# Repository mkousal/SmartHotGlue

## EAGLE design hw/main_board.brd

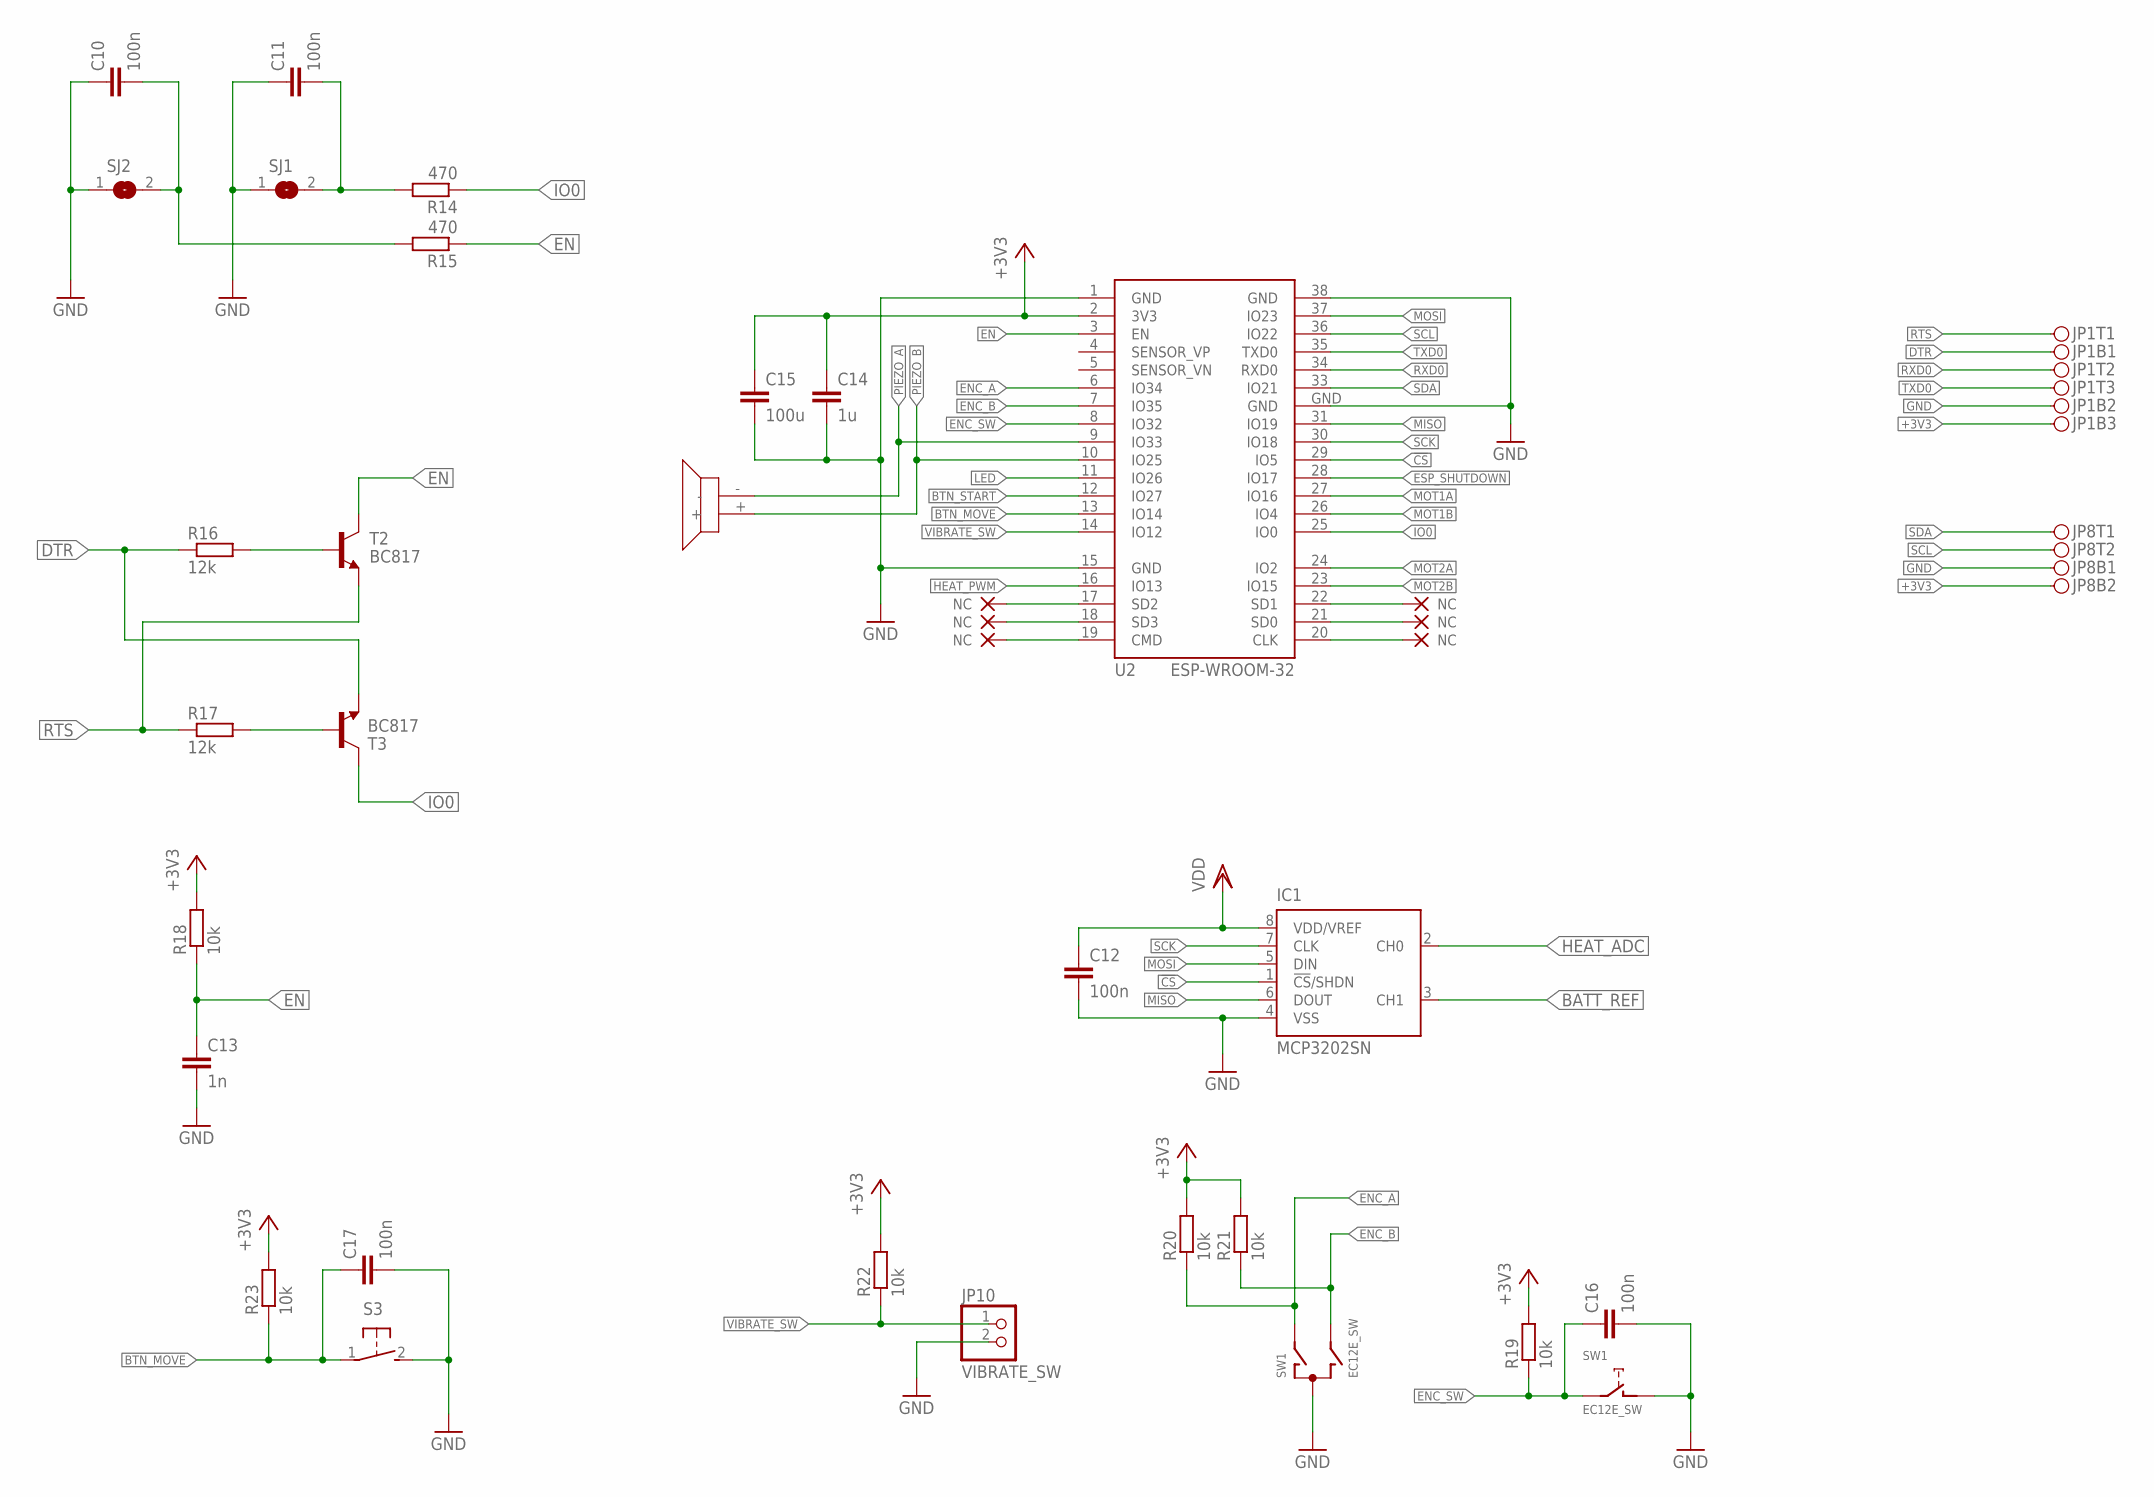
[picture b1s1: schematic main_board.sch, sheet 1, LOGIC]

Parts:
C10, C11, C12, C16, C17: 100n; C0603
C13: 1n; C0603
C14: 1u; C0603
C15: 100u; C0603
IC1: MCP3202SN; SO-08
JP1: PINH2X03; PINH2X03SMD
JP8: PINH2X02; PINH2X02SMD
JP10: VIBRATE_SW; 1X02
R14, R15: 470; R0603
R16, R17: 12k; R0603
R18, R19, R20, R21, R22, R23: 10k; R0603
S3: 31-XX; B3F-31XX
SJ1, SJ2: SJ
SW1: EC12E_SW; ALPS_EC12E_SW
T2, T3: BC817; SOT23-BEC
U2: ESP-WROOM-32
U$1: PIEZO

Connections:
!CS: IC1.1 (!CS!/SHDN), U2.29 (IO5)
+3V3: C14.1, C15.1, JP1.B3, JP8.B2, R18.2, R19.2, R20.2, R21.2, R22.2, R23.2, U2.2 (3V3); also elsewhere on the board
BATT_REF: IC1.3 (CH1); also elsewhere on the board
BTN_MOVE: C17.1, R23.1, S3.1, U2.13 (IO14)
BTN_START: U2.12 (IO27)
DTR: JP1.B1, R16.1, T3.E
EN: C13.1, R15.1, R18.1, T2.C, U2.3 (EN); also elsewhere on the board
ENC_A: R20.1, SW1.A, U2.6 (IO34)
ENC_B: R21.1, SW1.B, U2.7 (IO35)
ENC_SW: C16.1, R19.1, SW1.E (2), U2.8 (IO32)
ESP_SHUTDOWN: U2.28 (IO17); also elsewhere on the board
GND: C10.1, C11.1, C12.2, C13.2, C14.2, C15.2, C16.2, C17.2, IC1.4 (VSS), JP1.B2, JP8.B1, JP10.2, S3.2 (S), SJ1.1, SJ2.1, SW1.C, SW1.D (1), U2.1 (GND), U2.15 (GND), U2.38 (GND), U2.GND; also elsewhere on the board
HEAT_ADC: IC1.2 (CH0); also elsewhere on the board
HEAT_PWM: U2.16 (IO13); also elsewhere on the board
IO0: R14.1, T3.C, U2.25 (IO0)
LED: U2.11 (IO26)
MISO: IC1.6 (DOUT), U2.31 (IO19)
MOSI: IC1.5 (DIN), U2.37 (IO23)
MOT1A: U2.27 (IO16); also elsewhere on the board
MOT1B: U2.26 (IO4); also elsewhere on the board
MOT2A: U2.24 (IO2); also elsewhere on the board
MOT2B: U2.23 (IO15); also elsewhere on the board
unnamed: R16.2, T2.B
unnamed: C10.2, R15.2, SJ2.2
unnamed: R17.2, T3.B
unnamed: C11.2, R14.2, SJ1.2
PIEZO_A: U2.9 (IO33), U$1.-
PIEZO_B: U2.10 (IO25), U$1.+
RTS: JP1.T1, R17.1, T2.E
RXD0: JP1.T2, U2.34 (RXD0)
SCK: IC1.7 (CLK), U2.30 (IO18)
SCL: JP8.T2, U2.36 (IO22)
SDA: JP8.T1, U2.33 (IO21)
TXD0: JP1.T3, U2.35 (TXD0)
VDD: C12.1, IC1.8 (VDD/VREF); also elsewhere on the board
VIBRATE_SW: JP10.1, R22.1, U2.14 (IO12)

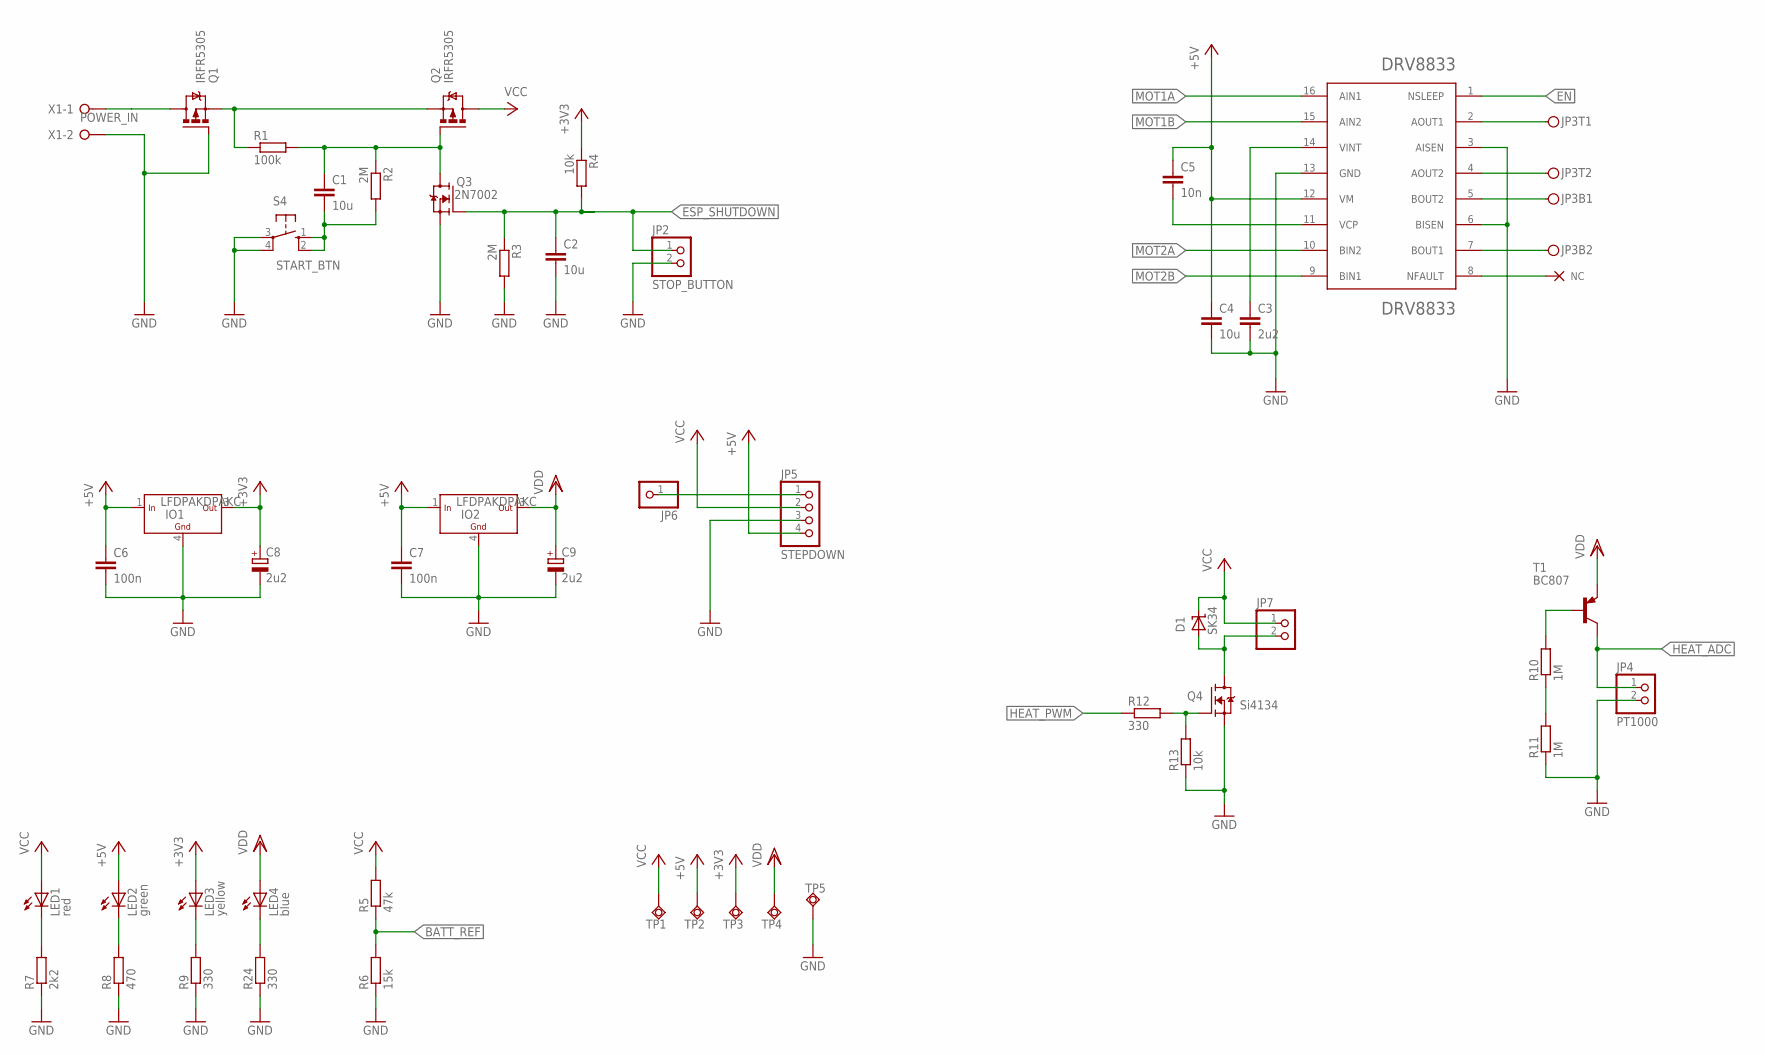
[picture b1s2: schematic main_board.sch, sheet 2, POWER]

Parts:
C1, C2: 10u; C0805
C3: 2u2; C0603
C4: 10u; C1206
C5: 10n; C0603
C6, C7: 100n; C0603
C8, C9: 2u2; UD-4X5,8_NICHICON
D1: SK34; SMB
DRV8833PWP1: DRV8833; SOP65P640X120-17N
IO1, IO2: LFDPAKDPAKC; DPAK
JP2: STOP_BUTTON; 1X02
JP3: PINH2X02; PINH2X02SMD
JP4: PT1000; 1X02
JP5: STEPDOWN; 1X04
JP6: PINHD-1X1; 1X01
JP7: PINHD-1X2; 1X02
LED1: red; CHIP-LED0603
LED2: green; CHIP-LED0603
LED3: yellow; CHIP-LED0603
LED4: blue; CHIP-LED0603
Q1, Q2: IRFR5305; D-PAK_TO252AA
Q3: 2N7002; SOT23
Q4: Si4134; SO-8
R1: 100k; R0603
R2, R3: 2M; R0603
R4, R13: 10k; R0603
R5: 47k; R0603
R6: 15k; R0603
R7: 2k2; R0603
R8: 470; R0603
R9, R12, R24: 330; R0603
R10, R11: 1M; R0603
S4: START_BTN; B3F-10XX
T1: BC807; SOT23-BEC
TP1, TP2, TP3, TP4, TP5: TPSQTP20SQ; TP20SQ
X1: POWER_IN; W237-132

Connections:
+3V3: C8.+, IO1.3 (OUT), LED3.A, R4.1, TP3.TP; also elsewhere on the board
+5V: C4.1, C5.1, C6.1, C7.1, DRV8833PWP1.12 (VM), IO1.1 (IN), IO2.1 (IN), JP5.4, LED2.A, TP2.TP
BATT_REF: R5.1, R6.2; also elsewhere on the board
EN: DRV8833PWP1.1 (NSLEEP); also elsewhere on the board
ESP_SHUTDOWN: C2.1, JP2.1, Q3.1 (G), R3.1, R4.2; also elsewhere on the board
GND: C2.2, C3.2, C4.2, C6.2, C7.2, C8.-, C9.-, DRV8833PWP1.3 (AISEN), DRV8833PWP1.6 (BISEN), DRV8833PWP1.13 (GND), IO1.4 (GND), IO2.4 (GND), JP2.2, JP4.2, JP5.3, Q1.1 (G), Q3.2 (S), Q4.1 (S), Q4.2 (S), Q4.3 (S), R3.2, R6.1, R7.1, R8.1, R9.1, R11.1, R13.1, R24.1, S4.3, S4.4 (P1), TP5.TP, X1.2; also elsewhere on the board
HEAT_ADC: JP4.1, T1.C; also elsewhere on the board
HEAT_PWM: R12.1; also elsewhere on the board
MOT1A: DRV8833PWP1.16 (AIN1); also elsewhere on the board
MOT1B: DRV8833PWP1.15 (AIN2); also elsewhere on the board
MOT2A: DRV8833PWP1.10 (BIN2); also elsewhere on the board
MOT2B: DRV8833PWP1.9 (BIN1); also elsewhere on the board
unnamed: Q1.3 (S), Q2.3 (S), R1.1
unnamed: C1.1, Q2.1 (G), Q3.3 (D), R1.2, R2.1
unnamed: LED4.C, R24.2
unnamed: Q1.4 (D), X1.1
unnamed: LED3.C, R9.2
unnamed: LED2.C, R8.2
unnamed: LED1.C, R7.2
unnamed: DRV8833PWP1.2 (AOUT1), JP3.T1
unnamed: DRV8833PWP1.4 (AOUT2), JP3.T2
unnamed: DRV8833PWP1.5 (BOUT2), JP3.B1
unnamed: DRV8833PWP1.7 (BOUT1), JP3.B2
unnamed: C3.1, DRV8833PWP1.14 (VINT)
unnamed: JP5.1, JP6.1
unnamed: C5.2, DRV8833PWP1.11 (VCP)
unnamed: D1.A, JP7.2, Q4.5 (D), Q4.6 (D), Q4.7 (D), Q4.8 (D)
unnamed: R10.1, R11.2
unnamed: R10.2, T1.B
unnamed: Q4.4 (G), R12.2, R13.2
unnamed: C1.2, R2.2, S4.1 (S), S4.2 (S1)
VCC: D1.C, JP5.2, JP7.1, LED1.A, Q2.4 (D), R5.2, TP1.TP
VDD: C9.+, IO2.3 (OUT), LED4.A, T1.E, TP4.TP; also elsewhere on the board

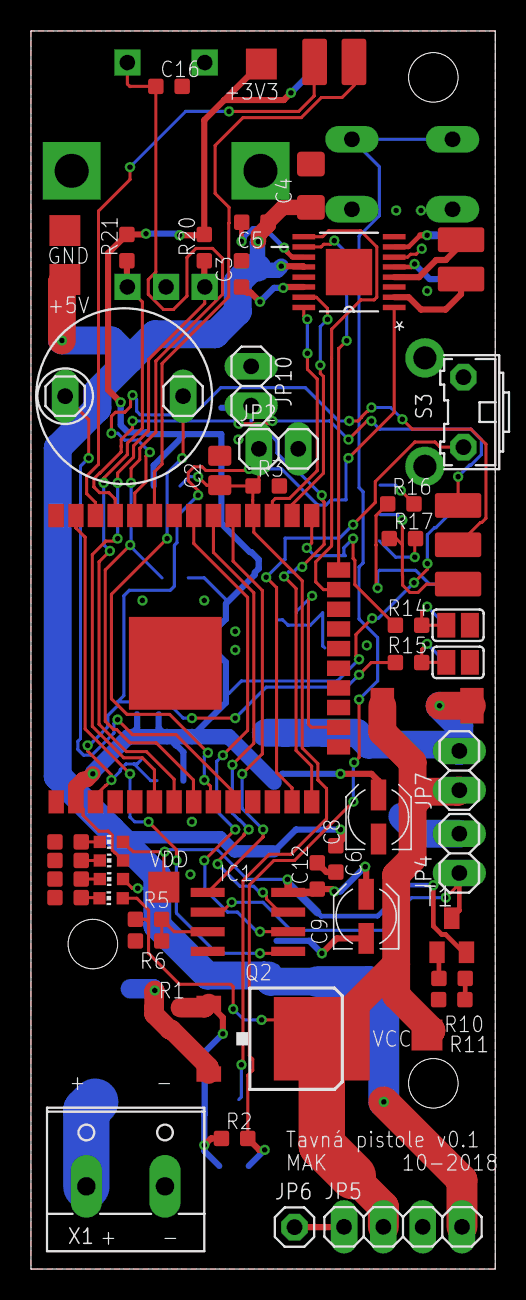
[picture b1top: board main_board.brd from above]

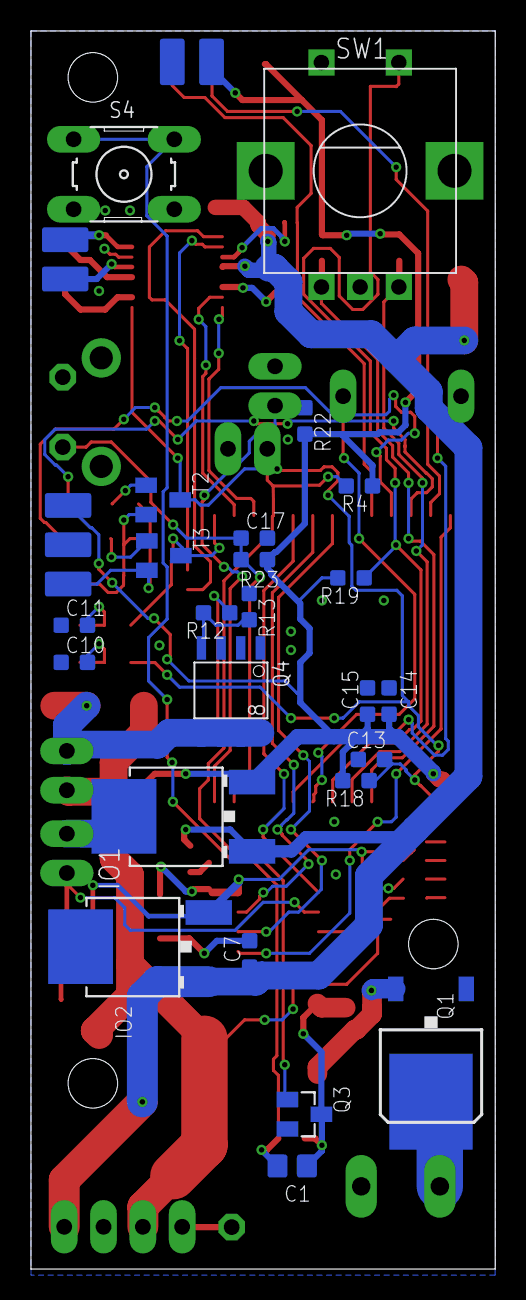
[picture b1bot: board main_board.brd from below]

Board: 2 copper layers, 30.0 x 80.0 mm, 79 parts (24 on the bottom side), 55 nets.

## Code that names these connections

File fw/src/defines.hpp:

#define CS_MCP3202 5
#define PIN_SDA 21
#define PIN_SCL 22
#define MOT_1A 16
#define MOT_1B 4
#define MOT_2A 2
#define MOT_2B 15 
#define ADC_CHANNEL_BAT 1 
#define ADC_CHANNEL_HEAT 0
#define VIB_SW 12
#define ENC_A 34 
#define ENC_B 35
#define ENC_SW 32
#define MOV_SW 14
#define HEAT_PWM 13
#define PIEZO_A 33
#define PIEZO_B 25
#define SHUTDOWN 17

const double A = 3.9083E-3;
const double B = -5.775E-7;
const double R0 = 1000.0;
const double RES = 4096.0;
const double I = 0.000475;
const double Uref = 3.3;
const double defined_a = (-R0*A);
const double defined_b = R0*R0*A*A;
const double defined_c = 4*R0*B;
const double defined_d = 2*R0*B;
const double defined_e = RES*I;

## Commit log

2018-12-11 Initial (late) commit
2018-12-13 Maybe finish work
    Updated and added menu things
    Motors now work
    Added removing of glue
2018-12-31 Add model of packaging
2019-01-22 Tune PID, make larger package
2019-01-22 Add thesis and gitignore
2019-01-28 Add UART and I2C chapter to thesis
2019-01-28 Add SPI chapter to thesis
2019-01-28 Add all EAGLE project files
2019-02-12 Shrinked schematic to A4 paper
2019-02-13 Final text and exported to PDF
2019-02-17 Add thanks to thesis
2019-05-16 Add presentation
2019-05-16 Fix mistake in presentation

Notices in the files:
parts and their libraries:
esp32: Creative Commons Attribution-ShareAlike 4.0 International
Copyright (C) PaJa 2001-2011
